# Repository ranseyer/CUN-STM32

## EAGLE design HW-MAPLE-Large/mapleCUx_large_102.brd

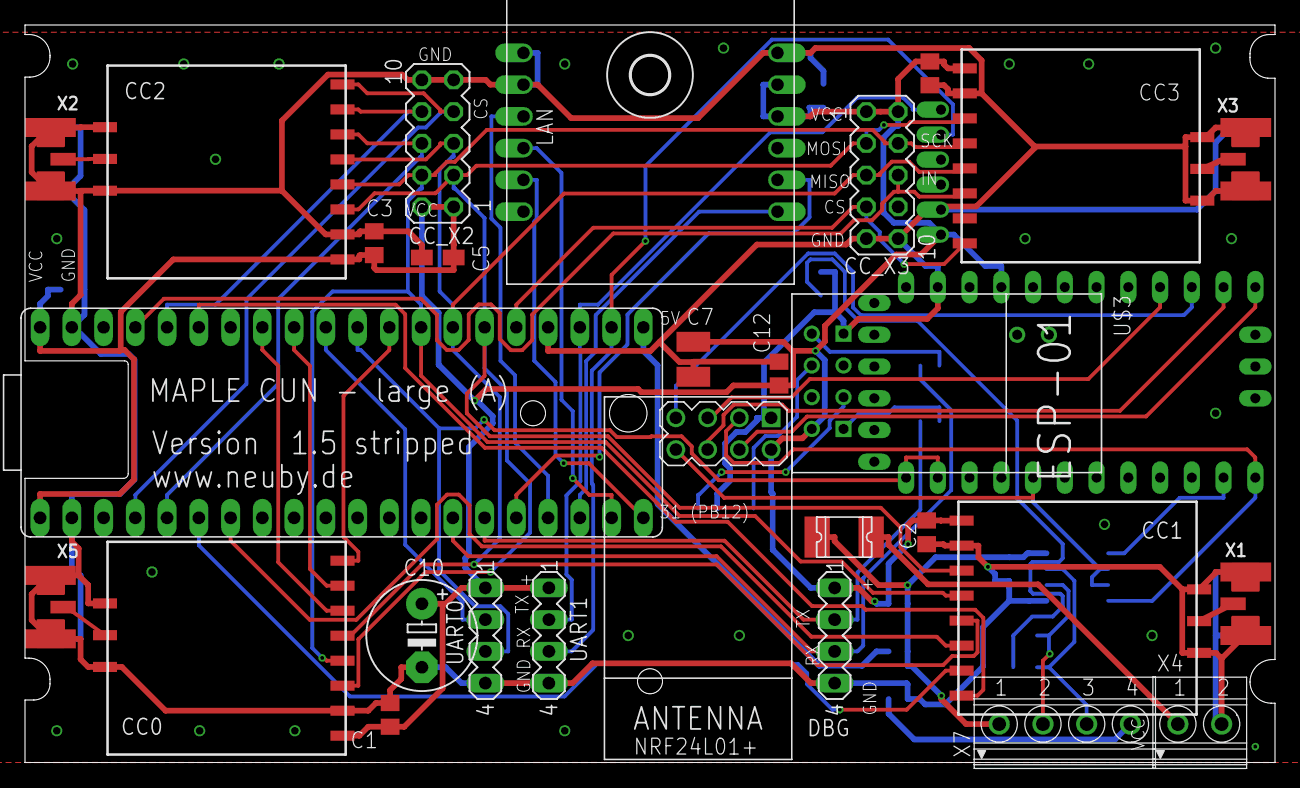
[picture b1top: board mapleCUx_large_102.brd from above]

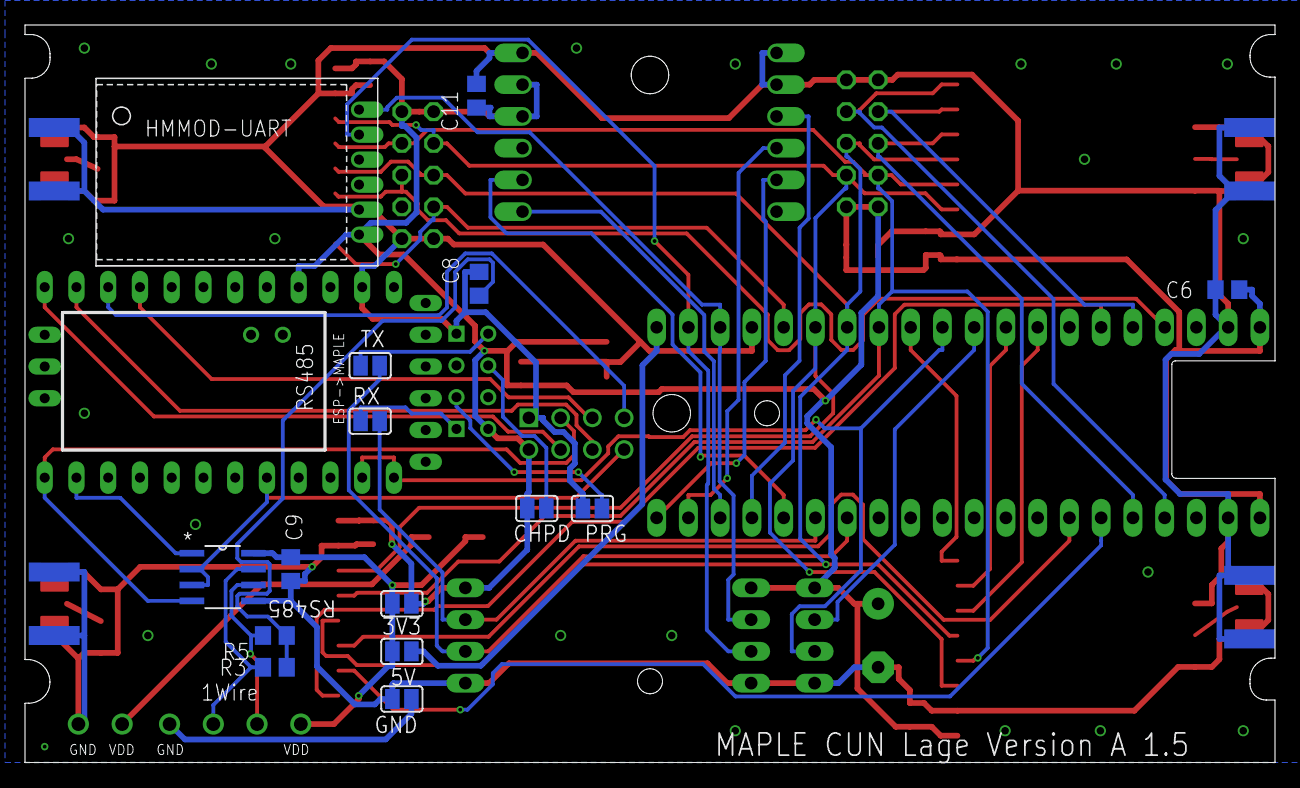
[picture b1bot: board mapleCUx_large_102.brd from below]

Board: 2 copper layers, 100.0 x 59.0 mm, 45 parts (15 on the bottom side), 49 nets.

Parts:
3V3, 5V: SJ
C1, C2, C3, C4, C6, C11, C12: 22pF; C0805
C5: 10uF; R/2012-12W
C7: 4,7; C1210
C8: 220p; C0805
C9: 22p; C0805
C10: 100uF; E5-8,5
CC0: CC1101; CC1101_MODULE1_SMD
CC1, CC2, CC4: CC1101_MODULE1SMD; CC1101_MODULE1_SMD
CC_X2, CC_X3: MA05-2
CHPD: SJ
DBG: MA04-1
F1: 1812L
GND: SJ
H6: MOUNT-HOLE3.0; 3,0
HMMOD-UART: HM-MOD-UARTDIL; HM-MOD-UART-DIL
IC2: LAN-USR-ES1; USR-ES1
NRF24L01+: NRF24L01+; WIRELESS-NRF24L01
PRG: SJ
R3, R5: 60; R0805
RS485: MAX487ECSA+; SOIC127P600X175-8N
RX: SJ
TX: SJ
U$1: MAPLEMINI; 20-DIP
U$2: ABK-PRO-MINI
U$3: ESP01
UART0, UART1: MA04-1
X1, X2, X3, X5: SMA_EDGELAUNCH_UFL
X4: 1751248
X7: 1751264

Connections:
1W: R5.2, RS485.6, X7.2
2W: R3.2, RS485.7, X7.3
+5V: 5V.2, U$1.21
CC_CS0: CC0.CSN, U$1.29
CC_CS1: CC1.CSN, U$1.35
CC_CS2: CC2.CSN, CC_X2.7, U$1.4
CC_CS3: CC4.CSN, CC_X3.7, U$1.25
CC_IN_0: CC0.GDO2, U$1.33
CC_IN_1: CC1.GDO2, U$1.7
CC_IN_2: CC2.GDO2, CC_X2.6, U$1.5
CC_IN_3: CC4.GDO2, CC_X3.6, U$1.37
CC_OUT_0: CC0.GDO0, U$1.32
CC_OUT_1: CC1.GDO0, U$1.6
CC_OUT_2: CC2.GDO0, CC_X2.8, U$1.36
CE-A: NRF24L01+.3, RS485.4, U$2.D9
CSN-A: NRF24L01+.4, U$2.D10
GD: GND.2, X7.4
GND: C1.1, C2.1, C3.1, C4.1, C5.-, C6.2, C7.1, C8.2, C9.1, C10.-, C11.1, C12.2, CC0.GND@0, CC0.GND@1, CC0.GND@2, CC1.GND@0, CC1.GND@1, CC1.GND@2, CC2.GND@0, CC2.GND@1, CC2.GND@2, CC4.GND@0, CC4.GND@1, CC4.GND@2, CC_X2.9, CC_X2.10, CC_X3.9, CC_X3.10, DBG.4, GND.1, HMMOD-UART.2, IC2.1, IC2.2, IC2.12, NRF24L01+.1, PRG.2, RS485.5, U$1.2, U$1.24, U$1.39, U$2.GND, U$3.GND, UART0.4, UART1.4, X1.GND@1, X1.GND@2, X1.GND@3, X1.GND@4, X2.GND@1, X2.GND@2, X2.GND@3, X2.GND@4, X3.GND@1, X3.GND@2, X3.GND@3, X3.GND@4, X4.2, X5.GND@1, X5.GND@2, X5.GND@3, X5.GND@4
IRQ-A: NRF24L01+.8, RS485.2, RS485.3, U$2.D2
MISO1: CC0.MISO, CC1.MISO, CC2.MISO, CC4.MISO, CC_X2.5, CC_X3.5, U$1.27
MISO2: IC2.7, U$1.18
MISO-A: NRF24L01+.7, U$2.D12
MOSI1: CC0.MOSI, CC1.MOSI, CC2.MOSI, CC4.MOSI, CC_X2.3, CC_X3.3, U$1.26
MOSI-A: NRF24L01+.6, U$2.D11
unnamed: CC1.ANT, X1.P
unnamed: CC4.ANT, X3.P
unnamed: CC2.ANT, X2.P
unnamed: CC0.ANT, X5.P
unnamed: RX.2, U$3.RX
unnamed: TX.2, U$3.TX
unnamed: PRG.1, U$3.GPIO0
unnamed: CHPD.2, U$3.CH_PD
unnamed: C8.1, R3.1, R5.1
unnamed: F1.P$2, X4.1
RO-A: RS485.1, U$2.D8
RST: IC2.3, U$1.17
RX1: HMMOD-UART.5, U$1.22, UART1.3
RX-MAPLE: U$1.30, U$2.RX1, U$2.TX0, UART0.3
RX_DBG: DBG.3, TX.1, U$1.14
SCK1: CC0.SCLK, CC1.SCLK, CC2.SCLK, CC4.SCLK, CC_X2.4, CC_X3.4, U$1.28
SCK2: IC2.4, U$1.19
SCK-A: NRF24L01+.5, U$2.D13
TX1: HMMOD-UART.6, U$1.23, UART1.2
TX-MAPLE: U$1.31, UART0.2
TX_DBG: DBG.2, RX.1, U$1.15
VCC: 3V3.1, C1.2, C2.2, C3.2, C4.2, C5.+, C6.1, C7.2, C10.+, C11.2, C12.1, CC0.VCC, CC1.VCC, CC2.VCC, CC4.VCC, CC_X2.1, CC_X2.2, CC_X3.1, CC_X3.2, CHPD.1, DBG.1, HMMOD-UART.1, IC2.10, IC2.11, NRF24L01+.2, U$1.1, U$1.40, U$2.VCC, U$3.VCC, UART0.1, UART1.1
VDD: 3V3.2, 5V.1, C9.2, F1.P$1, RS485.8, X7.1
WIZ_CS: IC2.5, U$1.20
WIZ_RST: IC2.8, U$1.16

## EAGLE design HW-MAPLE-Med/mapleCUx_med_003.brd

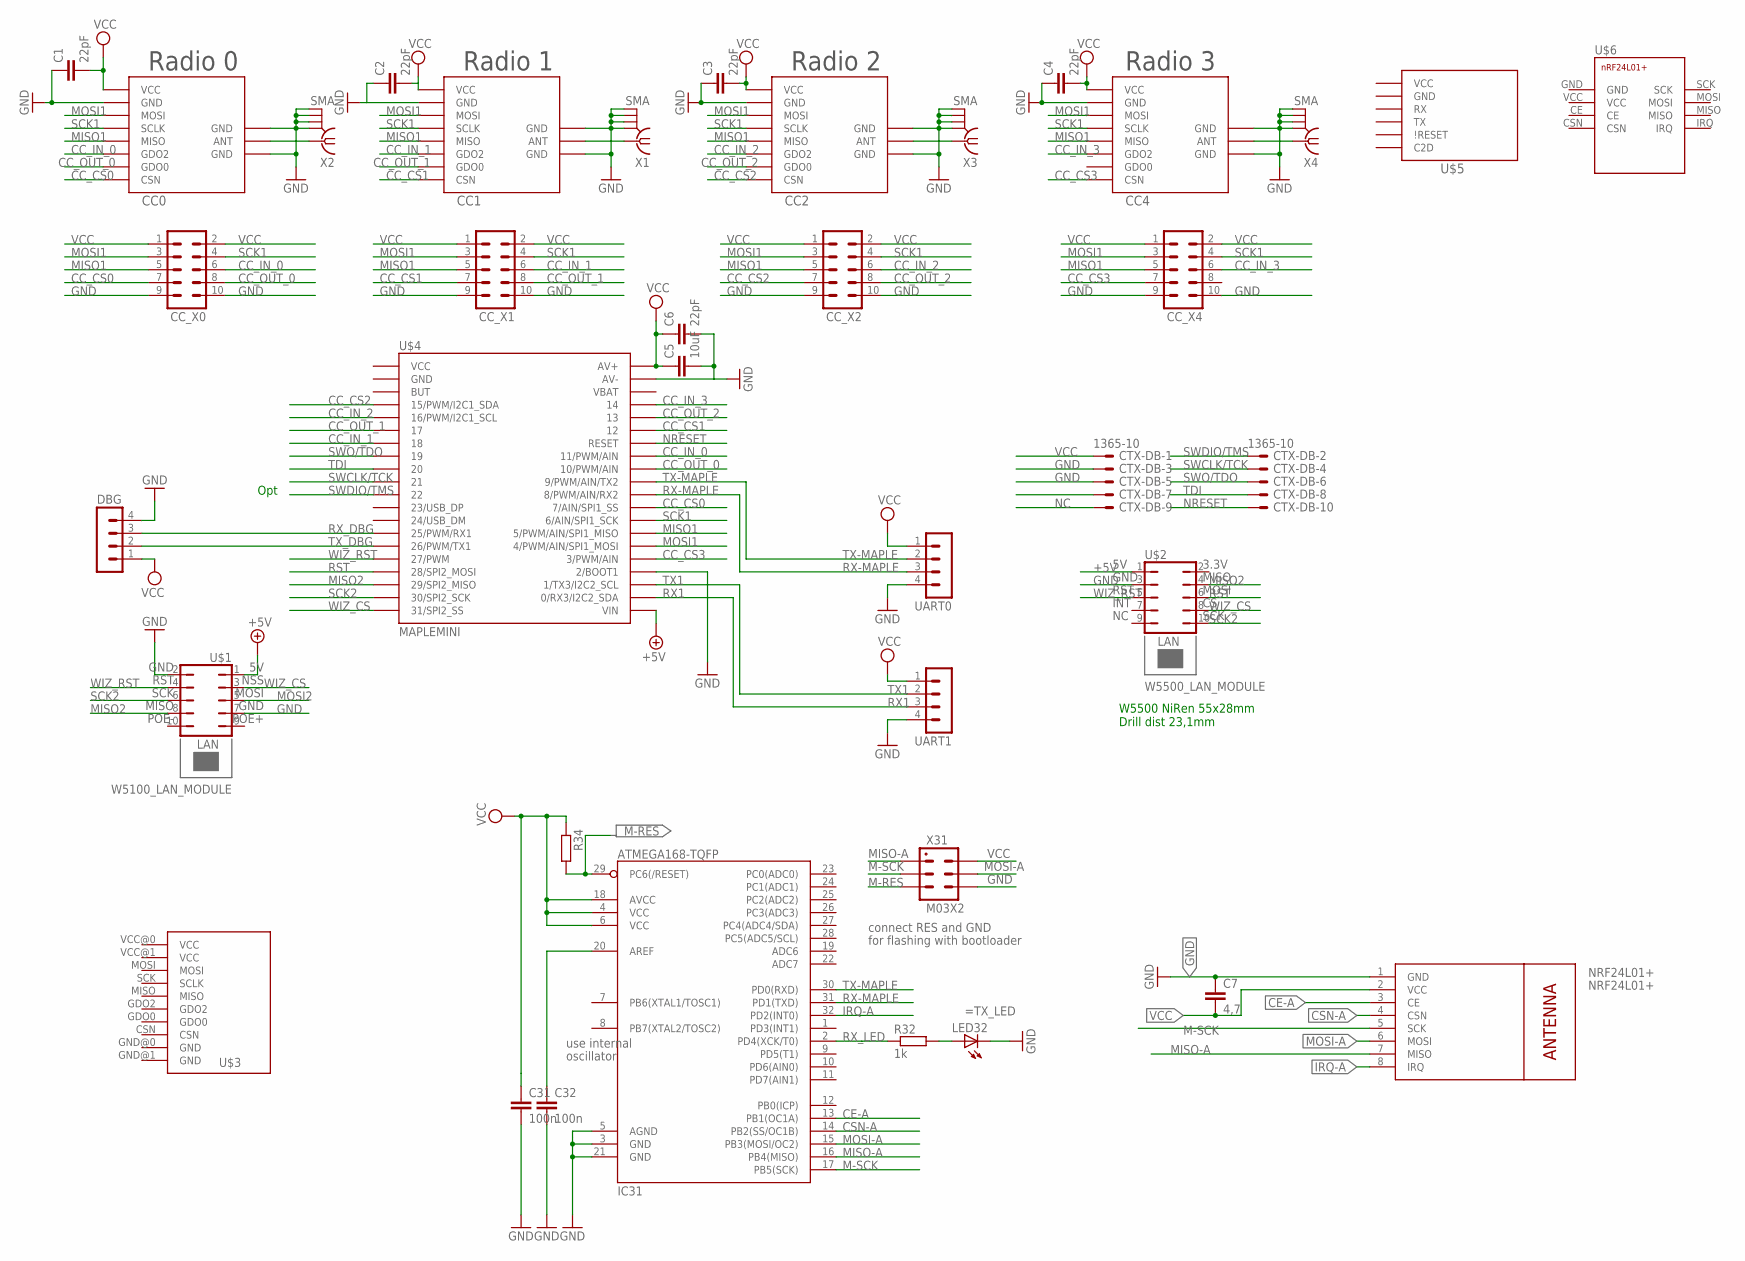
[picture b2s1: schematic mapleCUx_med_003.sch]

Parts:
C1, C2, C3, C4, C6: 22pF; C0805
C5: 10uF; C1210
C7: 4,7; C1210
C31, C32: 100n; C0805
CC0, CC1, CC2, CC4: CC1101_MODULE1SMD; CC1101_MODULE1_SMD
CC_X0, CC_X1, CC_X2, CC_X4: MA05-2
CTX-DB: 1365-10
DBG: MA04-1
IC31: ATMEGA168-TQFP; TQFP32-08
LED32: LEDCHIPLED_0805; CHIPLED_0805
NRF24L01+: NRF24L01+; WIRELESS-NRF24L01
R32: 1k; R0805
R34: R-EU_R0805; R0805
U$1: W5100_LAN_MODULE
U$2: W5500_LAN_MODULE; W5500_LAN_MODULE-1
U$3: CC1101_MODULE3_DIL
U$4: MAPLEMINI; 20-DIP
U$5: HM-MOD-UARTDIL; HM-MOD-UART-DIL
U$6: NRF24L01+SMD
UART0, UART1: MA04-1
X1, X2, X3, X4: SMA
X31: M03X2; 2X03-1.27MM_SMD

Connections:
+5V: U$1.1, U$2.1, U$4.21 (VIN)
CC_CS0: CC0.CSN, CC_X0.7, U$4.29 (7/AIN/SPI1_SS)
CC_CS1: CC1.CSN, CC_X1.7, U$4.35 (12)
CC_CS2: CC2.CSN, CC_X2.7, U$4.4 (15/PWM/I2C1_SDA)
CC_CS3: CC4.CSN, CC_X4.7, U$4.25 (3/PWM/AIN)
CC_IN_0: CC0.GDO2, CC_X0.6, U$4.33 (11/PWM/AIN)
CC_IN_1: CC1.GDO2, CC_X1.6, U$4.7 (18)
CC_IN_2: CC2.GDO2, CC_X2.6, U$4.5 (16/PWM/I2C1_SCL)
CC_IN_3: CC4.GDO2, CC_X4.6, U$4.37 (14)
CC_OUT_0: CC0.GDO0, CC_X0.8, U$4.32 (10/PWM/AIN)
CC_OUT_1: CC1.GDO0, CC_X1.8, U$4.6 (17)
CC_OUT_2: CC2.GDO0, CC_X2.8, U$4.36 (13)
CE-A: IC31.13 (PB1(OC1A)), NRF24L01+.3 (CE)
CSN-A: IC31.14 (PB2(SS/OC1B)), NRF24L01+.4 (CSN)
GND: C1.1, C2.1, C3.1, C4.1, C5.2, C6.2, C7.1, C31.2, C32.2, CC0.GND@0 (GND), CC0.GND@1 (GND), CC0.GND@2 (GND), CC1.GND@0 (GND), CC1.GND@1 (GND), CC1.GND@2 (GND), CC2.GND@0 (GND), CC2.GND@1 (GND), CC2.GND@2 (GND), CC4.GND@0 (GND), CC4.GND@1 (GND), CC4.GND@2 (GND), CC_X0.9, CC_X0.10, CC_X1.9, CC_X1.10, CC_X2.9, CC_X2.10, CC_X4.9, CC_X4.10, CTX-DB.3, CTX-DB.5, DBG.4, IC31.3 (GND), IC31.5 (AGND), IC31.21 (GND), LED32.C, NRF24L01+.1 (GND), U$1.2, U$1.7, U$2.3, U$3.GND@0 (GND), U$3.GND@1 (GND), U$4.24 (2/BOOT1), U$4.39 (AV-), U$5.2 (GND), U$6.GND, UART0.4, UART1.4, X1.GND@1 (2), X1.GND@2 (3), X1.GND@3 (4), X1.GND@4 (5), X2.GND@1 (2), X2.GND@2 (3), X2.GND@3 (4), X2.GND@4 (5), X3.GND@1 (2), X3.GND@2 (3), X3.GND@3 (4), X3.GND@4 (5), X4.GND@1 (2), X4.GND@2 (3), X4.GND@3 (4), X4.GND@4 (5), X31.P$6 (6)
IRQ-A: IC31.32 (PD2(INT0)), NRF24L01+.8 (IRQ)
M-RES: IC31.29 (PC6(/RESET)), R34.2, X31.P$5 (5)
M-SCK: IC31.17 (PB5(SCK)), NRF24L01+.5 (SCK), X31.P$3 (3)
MISO1: CC0.MISO, CC1.MISO, CC2.MISO, CC4.MISO, CC_X0.5, CC_X1.5, CC_X2.5, CC_X4.5, U$4.27 (5/PWM/AIN/SPI1_MISO)
MISO2: U$1.8, U$2.4, U$4.18 (29/SPI2_MISO)
MISO-A: IC31.16 (PB4(MISO)), NRF24L01+.7 (MISO), X31.P$1 (1)
MOSI1: CC0.MOSI, CC1.MOSI, CC2.MOSI, CC4.MOSI, CC_X0.3, CC_X1.3, CC_X2.3, CC_X4.3, U$4.26 (4/PWM/AIN/SPI1_MOSI)
MOSI2: U$1.5
MOSI-A: IC31.15 (PB3(MOSI/OC2)), NRF24L01+.6 (MOSI), X31.P$4 (4)
unnamed: CC2.ANT, X3.1
unnamed: CC4.ANT, X4.1
unnamed: CC1.ANT, X1.1
unnamed: CC0.ANT, X2.1
unnamed: LED32.A, R32.2
unnamed: C32.1, IC31.20 (AREF)
NC: CTX-DB.9
NRESET: CTX-DB.10, U$4.34 (RESET)
RST: U$2.6, U$4.17 (28/SPI2_MOSI)
RX1: U$4.22 (0/RX3/I2C2_SDA), UART1.3
RX-MAPLE: IC31.31 (PD1(TXD)), U$4.30 (8/PWM/AIN/RX2), UART0.3
RX_DBG: DBG.3, U$4.14 (25/PWM/RX1)
RX_LED: IC31.2 (PD4(XCK/T0)), R32.1
SCK1: CC0.SCLK, CC1.SCLK, CC2.SCLK, CC4.SCLK, CC_X0.4, CC_X1.4, CC_X2.4, CC_X4.4, U$4.28 (6/AIN/SPI1_SCK)
SCK2: U$1.6, U$2.10, U$4.19 (30/SPI2_SCK)
SWCLK/TCK: CTX-DB.4, U$4.10 (21)
SWDIO/TMS: CTX-DB.2, U$4.11 (22)
SWO/TDO: CTX-DB.6, U$4.8 (19)
TDI: CTX-DB.8, U$4.9 (20)
TX1: U$4.23 (1/TX3/I2C2_SCL), UART1.2
TX-MAPLE: IC31.30 (PD0(RXD)), U$4.31 (9/PWM/AIN/TX2), UART0.2
TX_DBG: DBG.2, U$4.15 (26/PWM/TX1)
VCC: C1.2, C2.2, C3.2, C4.2, C5.1, C6.1, C7.2, C31.1, CC0.VCC, CC1.VCC, CC2.VCC, CC4.VCC, CC_X0.1, CC_X0.2, CC_X1.1, CC_X1.2, CC_X2.1, CC_X2.2, CC_X4.1, CC_X4.2, CTX-DB.1, DBG.1, IC31.4 (VCC), IC31.6 (VCC), IC31.18 (AVCC), NRF24L01+.2 (VCC), R34.1, U$3.VCC@0 (VCC), U$3.VCC@1 (VCC), U$4.40 (AV+), U$5.1 (VCC), U$6.VCC, UART0.1, UART1.1, X31.P$2 (2)
WIZ_CS: U$1.3, U$2.8, U$4.20 (31/SPI2_SS)
WIZ_RST: U$1.4, U$2.5, U$4.16 (27/PWM)

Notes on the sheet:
Radio 1
Radio 0
Opt
Radio 2
Radio 3
W5500 NiRen 55x28mm Drill dist 23,1mm
use internal
oscillator
=TX_LED
connect RES and GND
for flashing with bootloader

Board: 2 copper layers, 37 parts (3 on the bottom side), 47 nets, no tracks yet.

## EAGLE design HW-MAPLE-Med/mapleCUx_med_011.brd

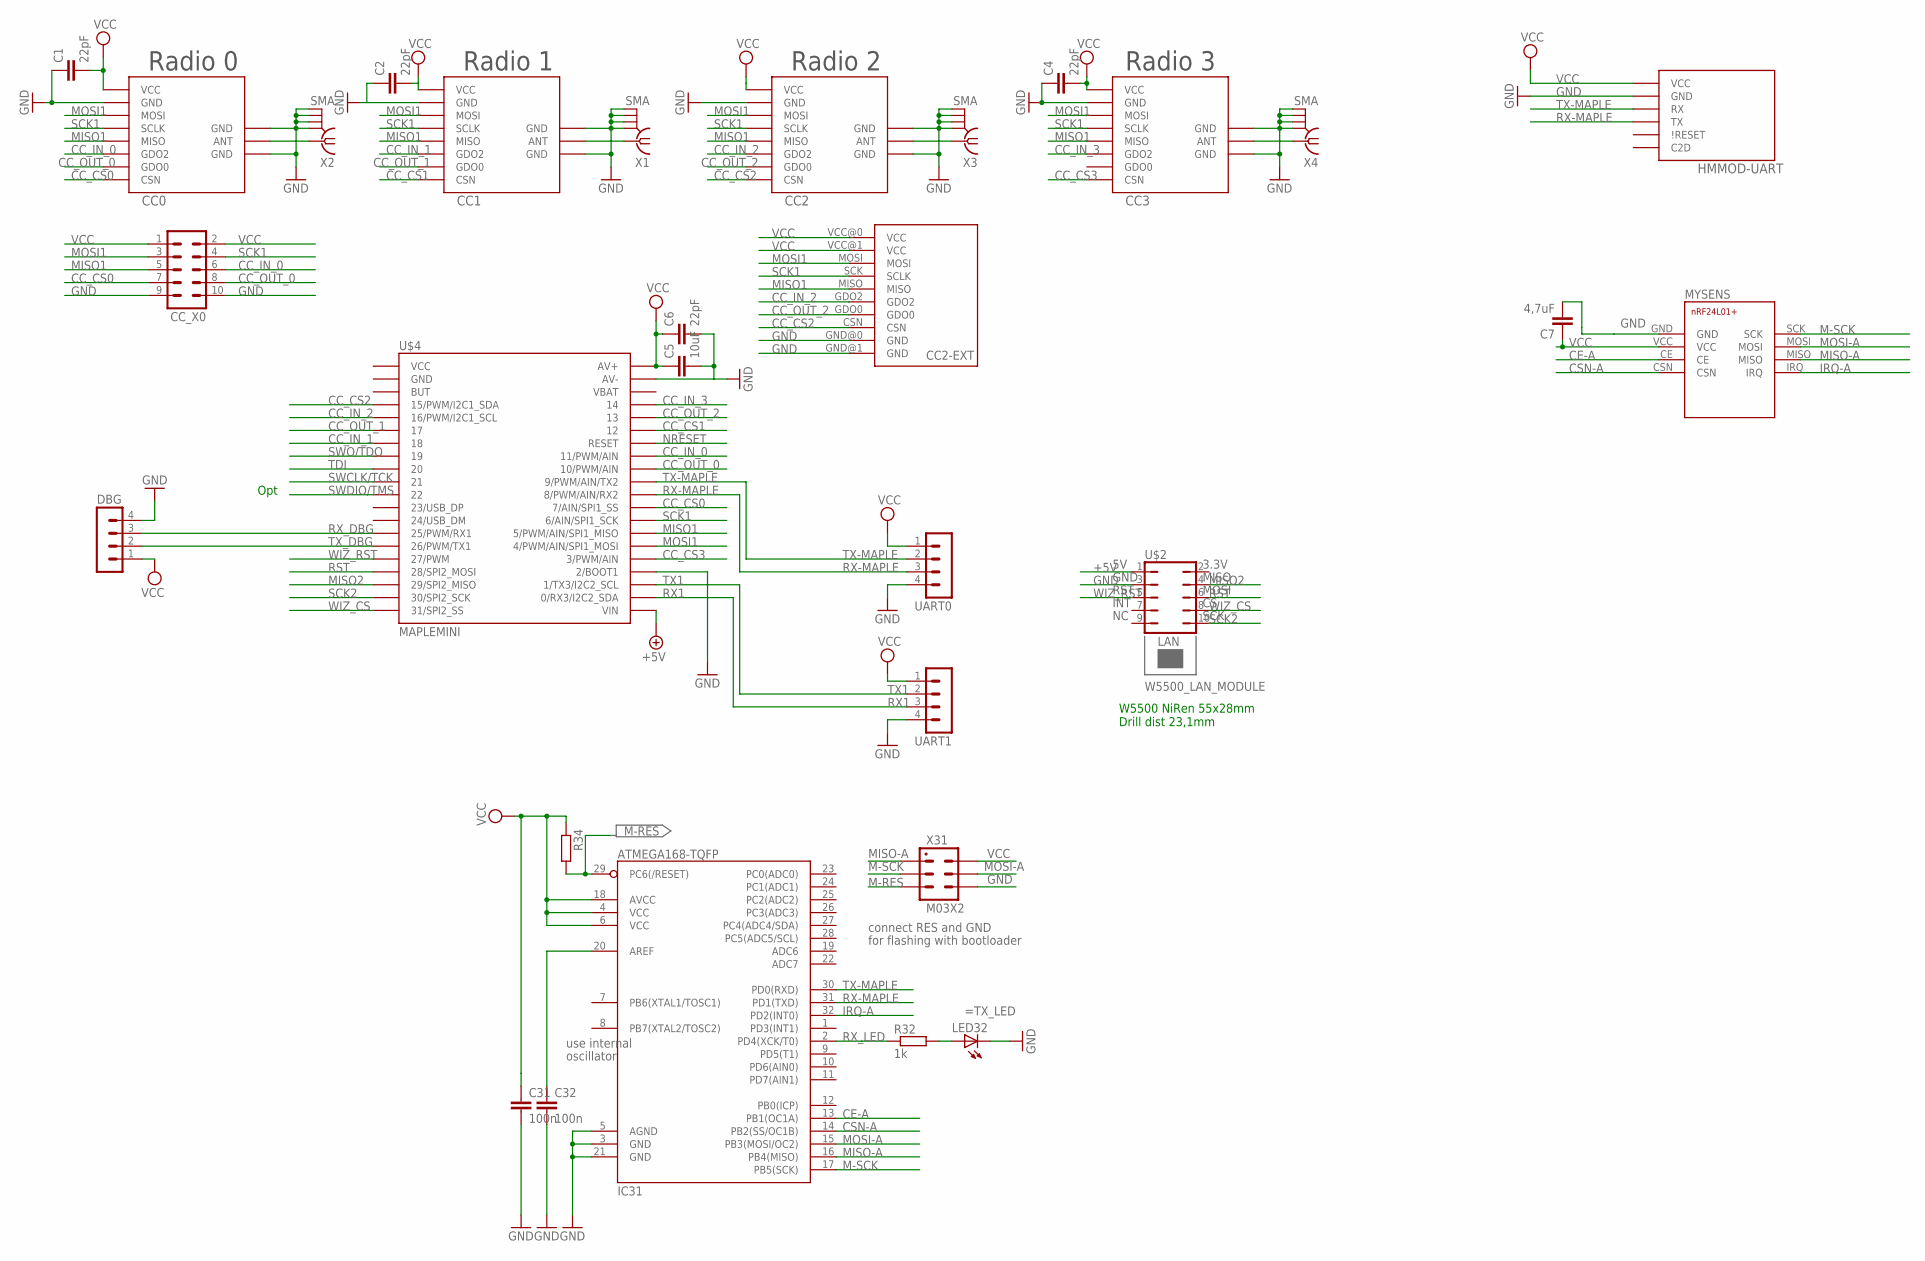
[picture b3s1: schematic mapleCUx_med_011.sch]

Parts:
C1, C2, C4, C6: 22pF; C0805
C5: 10uF; C1210
C7: 4,7uF; C1210
C31, C32: 100n; C0805
CC0, CC1, CC2, CC3: CC1101_MODULE1SMD; CC1101_MODULE1_SMD
CC2-EXT: CC1101_MODULE3_DIL
CC_X0: MA05-2
DBG: MA04-1
HMMOD-UART: HM-MOD-UARTDIL; HM-MOD-UART-DIL
IC31: ATMEGA168-TQFP; TQFP32-08
LED32: LEDCHIPLED_0805; CHIPLED_0805
MYSENS: NRF24L01+SMD
R32: 1k; R0805
R34: R-EU_R0805; R0805
U$2: W5500_LAN_MODULE; W5500_LAN_MODULE-1
U$4: MAPLEMINI; 20-DIP
UART0, UART1: MA04-1
X1, X2, X3, X4: SMA
X31: M03X2; 2X03-1.27MM_SMD

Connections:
+5V: U$2.1, U$4.21 (VIN)
CC_CS0: CC0.CSN, CC_X0.7, U$4.29 (7/AIN/SPI1_SS)
CC_CS1: CC1.CSN, U$4.35 (12)
CC_CS2: CC2.CSN, CC2-EXT.CSN, U$4.4 (15/PWM/I2C1_SDA)
CC_CS3: CC3.CSN, U$4.25 (3/PWM/AIN)
CC_IN_0: CC0.GDO2, CC_X0.6, U$4.33 (11/PWM/AIN)
CC_IN_1: CC1.GDO2, U$4.7 (18)
CC_IN_2: CC2.GDO2, CC2-EXT.GDO2, U$4.5 (16/PWM/I2C1_SCL)
CC_IN_3: CC3.GDO2, U$4.37 (14)
CC_OUT_0: CC0.GDO0, CC_X0.8, U$4.32 (10/PWM/AIN)
CC_OUT_1: CC1.GDO0, U$4.6 (17)
CC_OUT_2: CC2.GDO0, CC2-EXT.GDO0, U$4.36 (13)
CE-A: IC31.13 (PB1(OC1A)), MYSENS.CE
CSN-A: IC31.14 (PB2(SS/OC1B)), MYSENS.CSN
GND: C1.1, C2.1, C4.1, C5.2, C6.2, C7.2, C31.2, C32.2, CC0.GND@0 (GND), CC0.GND@1 (GND), CC0.GND@2 (GND), CC1.GND@0 (GND), CC1.GND@1 (GND), CC1.GND@2 (GND), CC2.GND@0 (GND), CC2.GND@1 (GND), CC2.GND@2 (GND), CC2-EXT.GND@0 (GND), CC2-EXT.GND@1 (GND), CC3.GND@0 (GND), CC3.GND@1 (GND), CC3.GND@2 (GND), CC_X0.9, CC_X0.10, DBG.4, HMMOD-UART.2 (GND), IC31.3 (GND), IC31.5 (AGND), IC31.21 (GND), LED32.C, MYSENS.GND, U$2.3, U$4.24 (2/BOOT1), U$4.39 (AV-), UART0.4, UART1.4, X1.GND@1 (2), X1.GND@2 (3), X1.GND@3 (4), X1.GND@4 (5), X2.GND@1 (2), X2.GND@2 (3), X2.GND@3 (4), X2.GND@4 (5), X3.GND@1 (2), X3.GND@2 (3), X3.GND@3 (4), X3.GND@4 (5), X4.GND@1 (2), X4.GND@2 (3), X4.GND@3 (4), X4.GND@4 (5), X31.P$6 (6)
IRQ-A: IC31.32 (PD2(INT0)), MYSENS.IRQ
M-RES: IC31.29 (PC6(/RESET)), R34.2, X31.P$5 (5)
M-SCK: IC31.17 (PB5(SCK)), MYSENS.SCK, X31.P$3 (3)
MISO1: CC0.MISO, CC1.MISO, CC2.MISO, CC2-EXT.MISO, CC3.MISO, CC_X0.5, U$4.27 (5/PWM/AIN/SPI1_MISO)
MISO2: U$2.4, U$4.18 (29/SPI2_MISO)
MISO-A: IC31.16 (PB4(MISO)), MYSENS.MISO, X31.P$1 (1)
MOSI1: CC0.MOSI, CC1.MOSI, CC2.MOSI, CC2-EXT.MOSI, CC3.MOSI, CC_X0.3, U$4.26 (4/PWM/AIN/SPI1_MOSI)
MOSI-A: IC31.15 (PB3(MOSI/OC2)), MYSENS.MOSI, X31.P$4 (4)
unnamed: CC2.ANT, X3.1
unnamed: CC3.ANT, X4.1
unnamed: CC1.ANT, X1.1
unnamed: CC0.ANT, X2.1
unnamed: LED32.A, R32.2
unnamed: C32.1, IC31.20 (AREF)
NRESET: U$4.34 (RESET)
RST: U$2.6, U$4.17 (28/SPI2_MOSI)
RX1: U$4.22 (0/RX3/I2C2_SDA), UART1.3
RX-MAPLE: HMMOD-UART.5 (TX), IC31.31 (PD1(TXD)), U$4.30 (8/PWM/AIN/RX2), UART0.3
RX_DBG: DBG.3, U$4.14 (25/PWM/RX1)
RX_LED: IC31.2 (PD4(XCK/T0)), R32.1
SCK1: CC0.SCLK, CC1.SCLK, CC2.SCLK, CC2-EXT.SCK (SCLK), CC3.SCLK, CC_X0.4, U$4.28 (6/AIN/SPI1_SCK)
SCK2: U$2.10, U$4.19 (30/SPI2_SCK)
SWCLK/TCK: U$4.10 (21)
SWDIO/TMS: U$4.11 (22)
SWO/TDO: U$4.8 (19)
TDI: U$4.9 (20)
TX1: U$4.23 (1/TX3/I2C2_SCL), UART1.2
TX-MAPLE: HMMOD-UART.6 (RX), IC31.30 (PD0(RXD)), U$4.31 (9/PWM/AIN/TX2), UART0.2
TX_DBG: DBG.2, U$4.15 (26/PWM/TX1)
VCC: C1.2, C2.2, C4.2, C5.1, C6.1, C7.1, C31.1, CC0.VCC, CC1.VCC, CC2.VCC, CC2-EXT.VCC@0 (VCC), CC2-EXT.VCC@1 (VCC), CC3.VCC, CC_X0.1, CC_X0.2, DBG.1, HMMOD-UART.1 (VCC), IC31.4 (VCC), IC31.6 (VCC), IC31.18 (AVCC), MYSENS.VCC, R34.1, U$4.40 (AV+), UART0.1, UART1.1, X31.P$2 (2)
WIZ_CS: U$2.8, U$4.20 (31/SPI2_SS)
WIZ_RST: U$2.5, U$4.16 (27/PWM)

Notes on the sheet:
Radio 1
Radio 0
Opt
Radio 2
Radio 3
W5500 NiRen 55x28mm Drill dist 23,1mm
use internal
oscillator
=TX_LED
connect RES and GND
for flashing with bootloader

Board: 2 copper layers, 30 parts (12 on the bottom side), 42 nets, no tracks yet.

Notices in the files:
parts and their libraries:
diy-modules: Released under the Creative Commons Attribution 4.0 International License: http://creativecommons.org/licenses/by/4.0
